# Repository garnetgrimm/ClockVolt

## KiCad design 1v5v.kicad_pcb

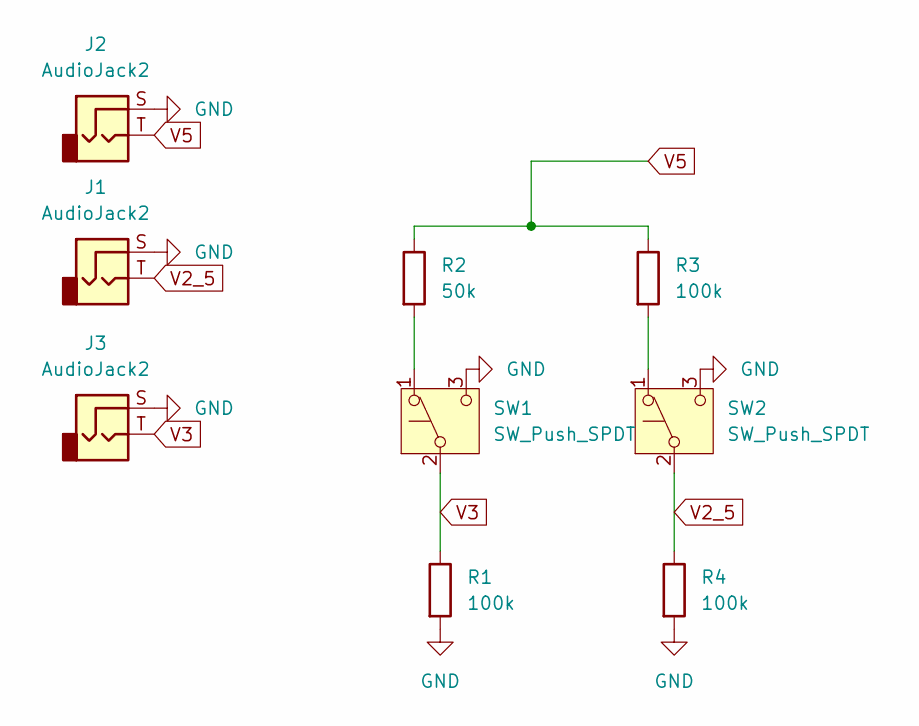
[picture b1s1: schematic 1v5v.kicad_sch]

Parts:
J1, J2, J3: AudioJack2; Jack_3.5mm_QingPu_WQP-PJ398SM_Vertical
R1, R3, R4: 100k; R_0805_2012Metric
R2: 50k; R_0805_2012Metric
SW1, SW2: SW_Push_SPDT; ANT11SECQE

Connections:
GND: J1.S, J2.S, J3.S, R1.2, R4.2, SW1.3 (C), SW2.3 (C)
unnamed: R2.2, SW1.1 (A)
unnamed: R3.2, SW2.1 (A)
V2_5: J1.T, R4.1, SW2.2 (B)
V3: J3.T, R1.1, SW1.2 (B)
V5: J2.T, R2.1, R3.1

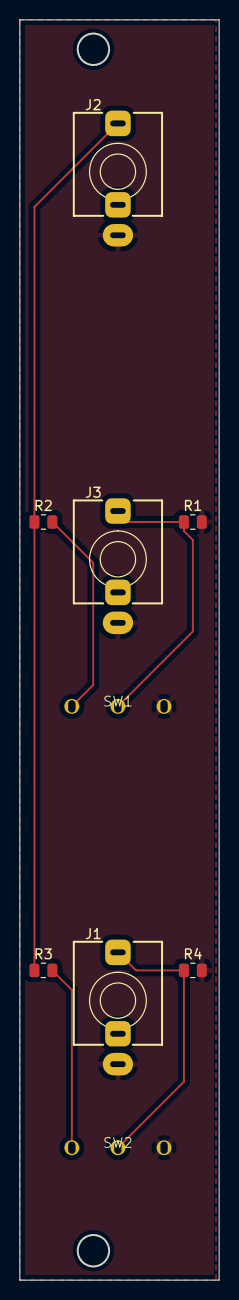
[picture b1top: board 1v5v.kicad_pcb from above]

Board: 2 copper layers, 20.2 x 128.4 mm, 9 parts (0 on the bottom side), 6 nets.

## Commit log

2024-06-04 init
2024-06-04 thonk footprint
